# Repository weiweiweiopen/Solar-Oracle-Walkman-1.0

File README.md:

# Solar Oracle Walkman 1.0

**A portable, open-source instrument for exploring the electrical identity of handmade dye-sensitized solar cells (DSSCs).** Solar Oracle Walkman brings together I–V measurement, an e-paper display, interchangeable glass cells and a transparent SLA enclosure. A charging variant investigates harvesting energy from the same cell that is measured.

[Build guide](docs/build-guide.md) · [SLA assembly](docs/assembly.md) · [Verification and limitations](docs/reproducibility.md) · [Image gallery](docs/gallery.md) · [DSSC enrollment / verification library](https://github.com/weiweiweiopen/Solar-Oracle-Walkman-DSSC-Enrollment-and-Verification-Library)

The photograph shows a physical prototype. The source packages below distinguish the USB measurement board, the charging-board development revision and the earlier three-capacitor design. **This is an open development release, not a certified or fully validated production kit.**

## Choose a matched variant

| Variant | Electronics | Matching enclosure | Status |
|---|---|---|---|
| **CHARGE / ADG706** | November 3 1206 revision; 92 footprints, two copper layers; two 1.5 F supercapacitors, AEM10941, TPS61023 and K1 | R19_CHARGE_SUPERCAP | Latest charging hardware/CAD source; complete charging firmware and physical qualification remain open |
| **RAW / USB** | November 3 1206 revision; 39 footprints, two copper layers; no harvester, capacitors or K1 | R19_RAW | Separate USB measurement variant; see its firmware build and calibration status |
| **Legacy ADS122C04** | Earlier four-layer, 175-footprint, three-capacitor relay design | Do not use the R19 packages without a new fit review | Original project retained for reference; GPIO/startup firmware only |

Do not mix boards, GPIO definitions, BOMs or enclosure variants. The three-capacitor render is not the latest two-capacitor charging board, and its 4.5 F energy estimates do not apply to the current design.

## Hardware and fabrication files

| Download | CHARGE / ADG706 | RAW / USB |
|---|---|---|
| Native KiCad project | [Open project](hardware/charge-adg706/KiCad/Marc_USB.kicad_pro) | [Open project](hardware/raw/KiCad/Marc_USB.kicad_pro) |
| PCB source | [PCB](hardware/charge-adg706/KiCad/Marc_USB.kicad_pcb) | [PCB](hardware/raw/KiCad/Marc_USB.kicad_pcb) |
| Schematics and local libraries | [KiCad folder](hardware/charge-adg706/KiCad/) | [KiCad folder](hardware/raw/KiCad/) |
| Gerber + drill package | [Fabrication ZIP](hardware/charge-adg706/fabrication/Marc_USB_charge_adg706_single_DSSC_1206_20261103.zip) | [Fabrication ZIP](hardware/raw/fabrication/Marc_USB_raw_single_DSSC_1206_20261103.zip) |
| BOM and assembly references | [Assembly folder](hardware/charge-adg706/assembly/) | [Assembly folder](hardware/raw/assembly/) |
| DRC / ERC results | [Checks](hardware/charge-adg706/verification/) | [Checks](hardware/raw/verification/) |

Use **KiCad 10** with its standard libraries. Local symbols, footprints and model dependencies are included. The Gerber ZIPs are PCB fabrication outputs, not complete turnkey PCBA orders: missing/TBD procurement fields, assembly choices and DRC dispositions must be resolved before ordering.

## SLA enclosure — editable and printable

| Download | CHARGE_SUPERCAP | RAW |
|---|---|---|
| Two-part print ZIP, mm / 1:1 | [STL](enclosure/R19_CHARGE_SUPERCAP/R19_CHARGE_SUPERCAP_STL.zip) | [STL](enclosure/R19_RAW/R19_RAW_STL.zip) |
| Native FreeCAD assembly | [FCStd](enclosure/R19_CHARGE_SUPERCAP/R19_CHARGE_SUPERCAP.FCStd) | [FCStd](enclosure/R19_RAW/R19_RAW.FCStd) |
| Individual and assembled STEP | [STEP](enclosure/R19_CHARGE_SUPERCAP/STEP/) | [STEP](enclosure/R19_RAW/STEP/) |
| Editable source: CAD, Blender, geometry inputs, scripts and QA | [Source ZIP](enclosure/R19_CHARGE_SUPERCAP/R19_CHARGE_SUPERCAP_editable_source.zip) | [Source ZIP](enclosure/R19_RAW/R19_RAW_editable_source.zip) |
| Dimensions and original design notes | [Notes](enclosure/R19_CHARGE_SUPERCAP/README.md) | [Notes](enclosure/R19_RAW/README.md) |

R19 uses a removable full upper cover, 16 magnets and two conductive zebra strips. Its footprint is 84 × 142.4 mm. Use the [assembly guide](docs/assembly.md) for glass dimensions, fasteners, print precautions and the PCB insertion sequence. The archives include editable sources, not just presentation meshes.

## Firmware and first build

The [RAW firmware source](firmware/current/README.md) compiled successfully with PlatformIO; its 14 GPIOs and 16 nominal load values match the current RAW PCB. Start with the [build guide](docs/build-guide.md). Firmware is board-specific; flashing a similarly named ESP32 program is not a substitute for checking the GPIO map, ADC, load sequence and display revision. The legacy [GPIO/startup layer](firmware/README.md) is **not** the full measurement application for either current board.

## Front and rear renders

Charging concept visualization from the Murata presentation material. These show the two-capacitor arrangement; the current manufacturing geometry is defined by the KiCad and R19 files above, not by the rendered enclosure.

The [gallery](docs/gallery.md) also includes the earlier front and rear renders with **three blue supercapacitors**, kept separately for visual and design history.

## Verification before manufacture

Fresh checks of the packaged designs found:

- Both PCBs: **0 unrouted connections, 0 schematic/PCB parity differences, 0 ERC findings**.
- RAW: **10 courtyard-overlap errors, 5 warnings**. CHARGE: **10 courtyard-overlap errors, 9 warnings**. These are disclosed, not suppressed or called a clean DRC.
- Four enclosure parts: native CAD reopened as valid single solids; all four print meshes are closed, with no nonmanifold edges or self-intersections detected.
- Each R19 embedded PCB snapshot exactly matches the corresponding packaged current board.

Geometry checks and software compilation do not establish printed fit, electrical safety, calibration, cold-start performance, charge-cycle endurance or PUF security. See [reproducibility status](docs/reproducibility.md) for the outstanding work needed for an independently validated build.

## Credits and license

Developed by Shih Wei Chieh / Wise Mouse Culture, building on [Marc Dusseiller's I–V tester lineage](https://github.com/weiweiweiopen/IVcurve_tester). Existing MIT attribution is preserved in [LICENSE](LICENSE). Third-party libraries and model assets retain their own terms; see [THIRD_PARTY_NOTICES.md](THIRD_PARTY_NOTICES.md).

The separate [Solar Oracle Walkman data library](https://weiweiweiopen.github.io/Solar-Oracle-Walkman-DSSC-Enrollment-and-Verification-Library/) provides the measurement-library context; it is not the hardware manufacturing package.

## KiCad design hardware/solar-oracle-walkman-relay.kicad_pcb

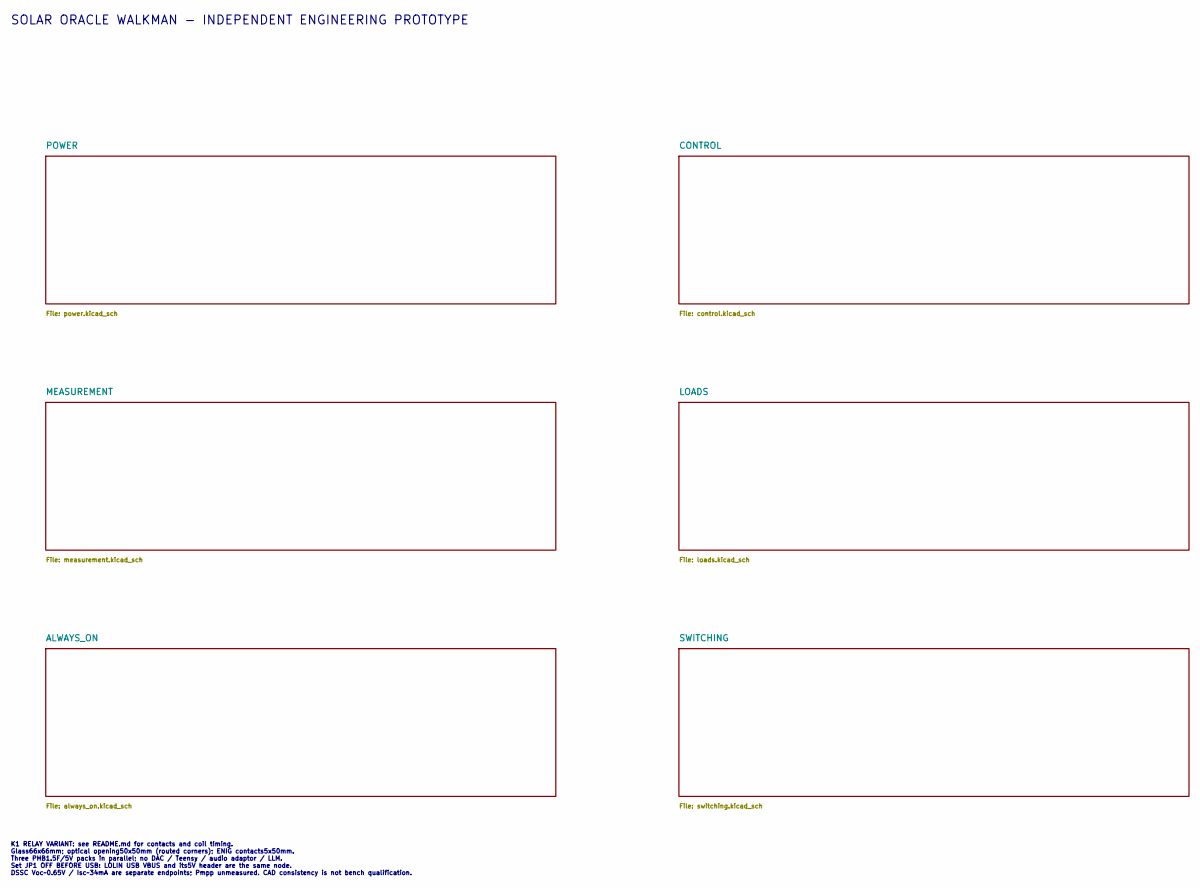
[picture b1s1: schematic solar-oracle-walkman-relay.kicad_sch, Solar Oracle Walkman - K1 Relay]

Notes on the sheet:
SOLAR ORACLE WALKMAN - INDEPENDENT ENGINEERING PROTOTYPE
K1 RELAY VARIANT: see README.md for contacts and coil timing. Glass66x66mm; optical opening50x50mm (routed corners); ENIG contacts5x50mm. Three PHB1.5F/5V packs in parallel; no DAC / Teensy / audio adaptor / LLM. Set JP1 OFF BEFORE USB: LOLIN USB VBUS and its5V header are the same node. DSSC Voc~0.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

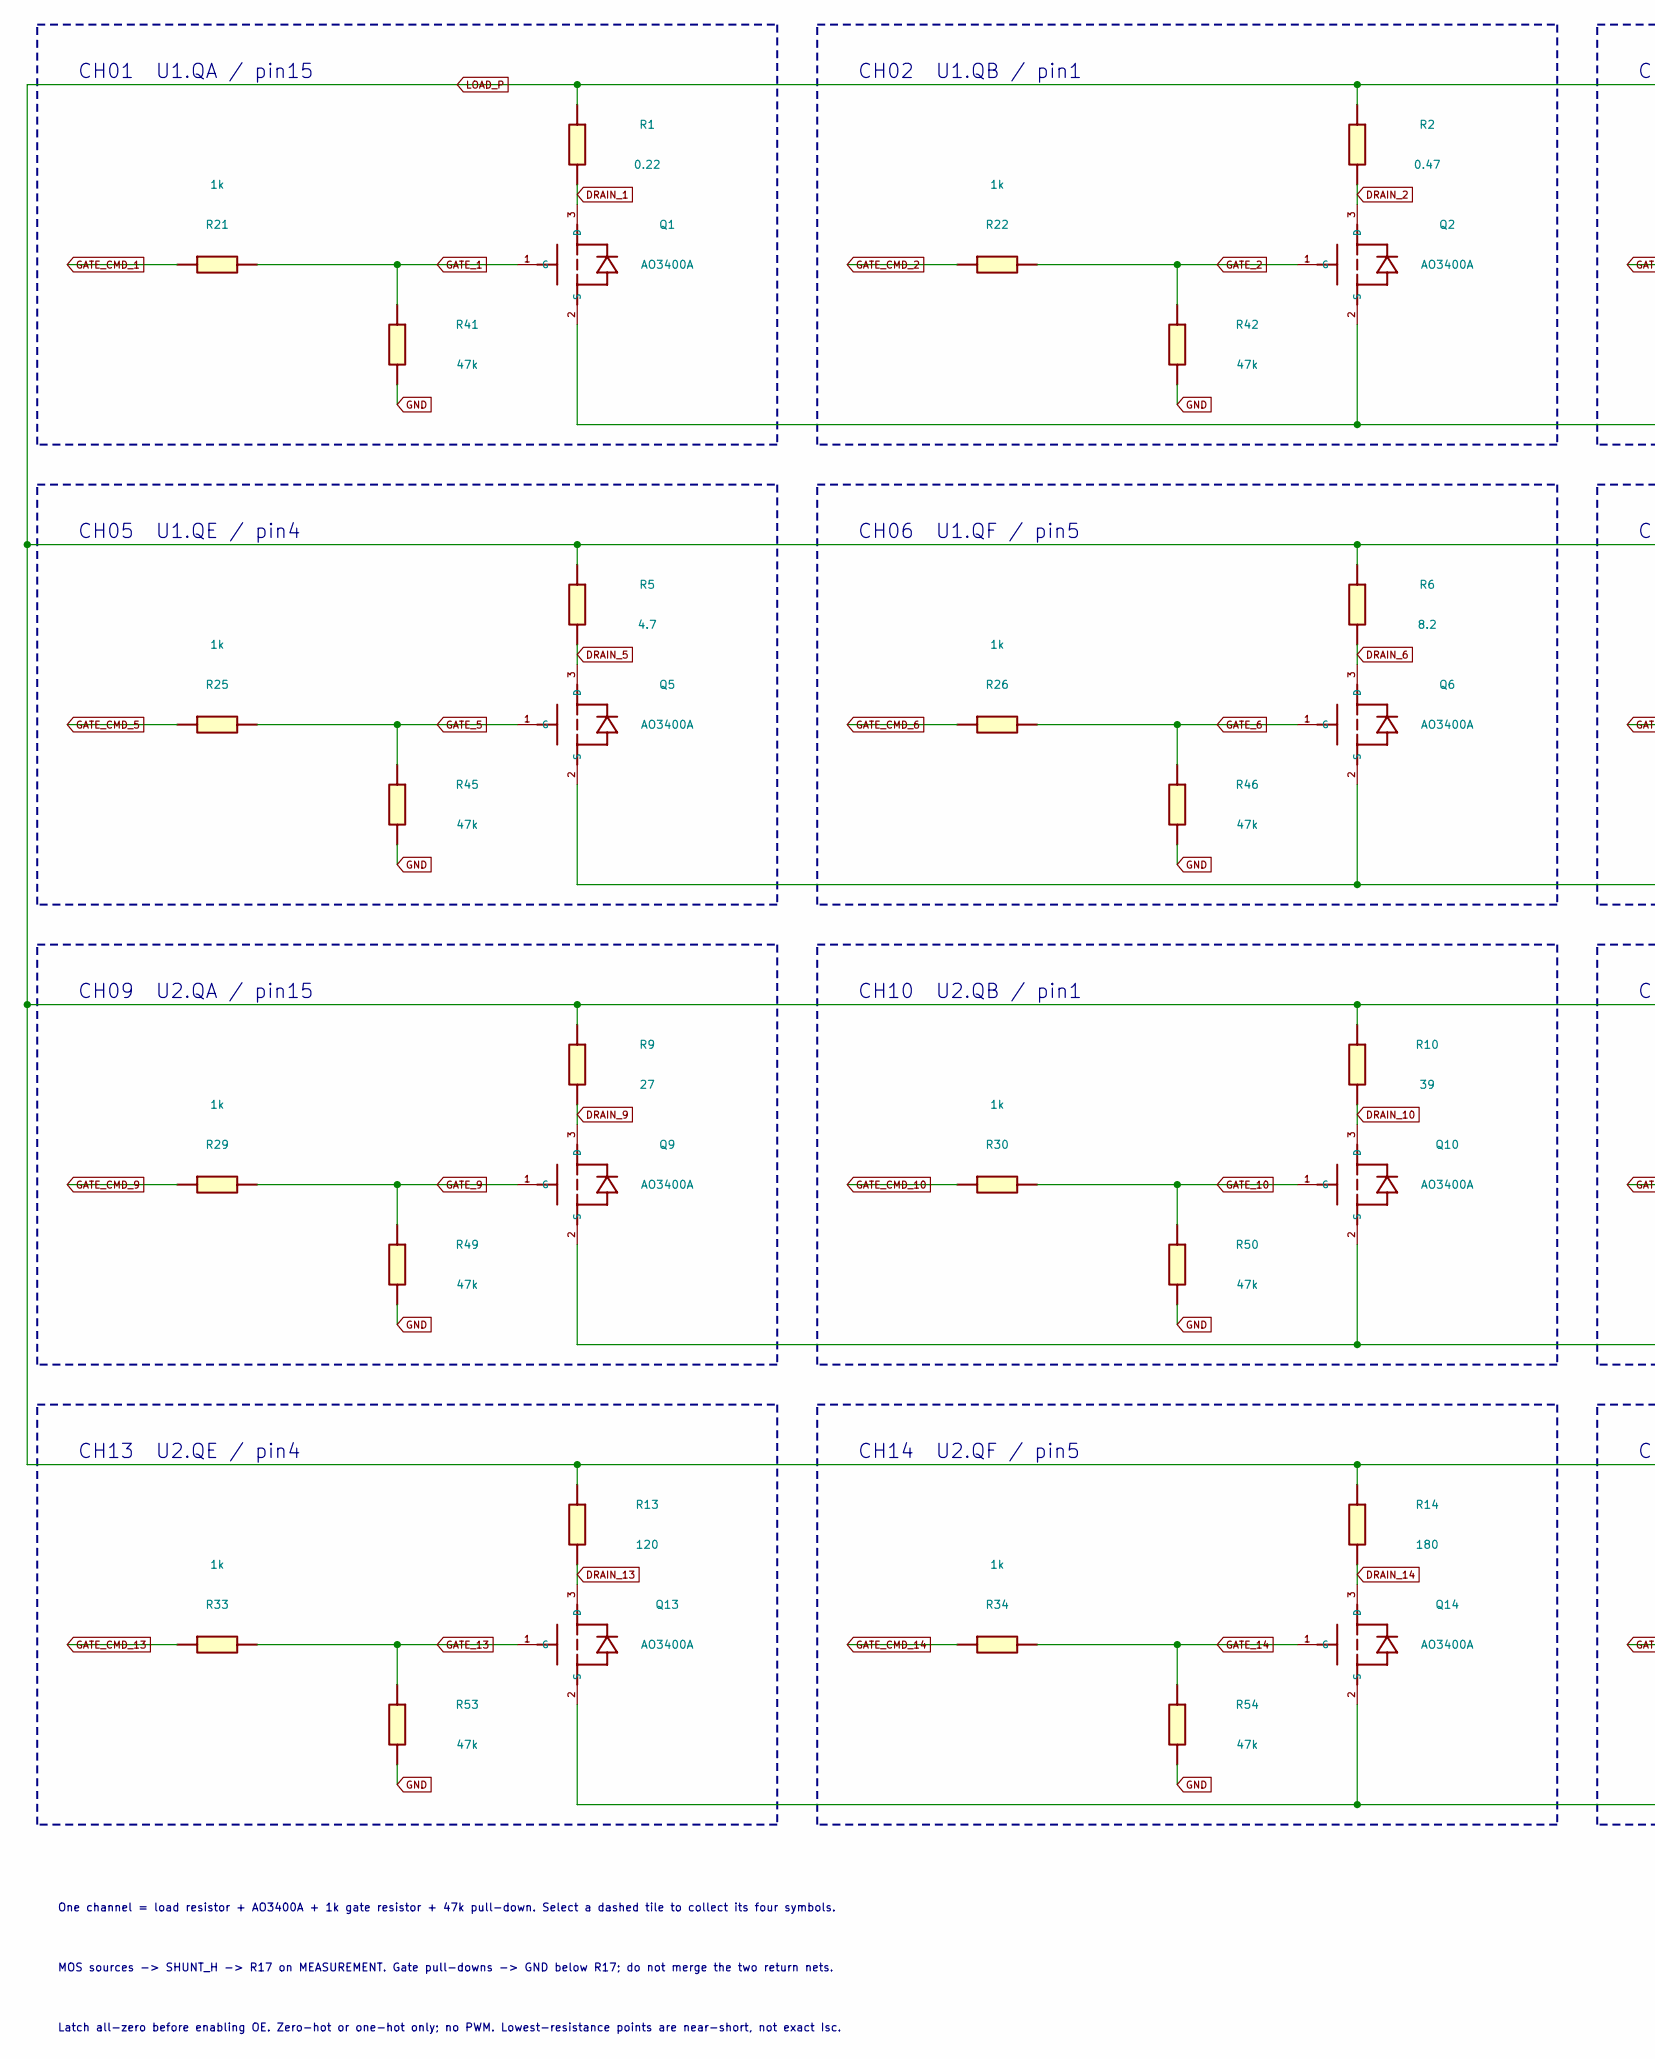
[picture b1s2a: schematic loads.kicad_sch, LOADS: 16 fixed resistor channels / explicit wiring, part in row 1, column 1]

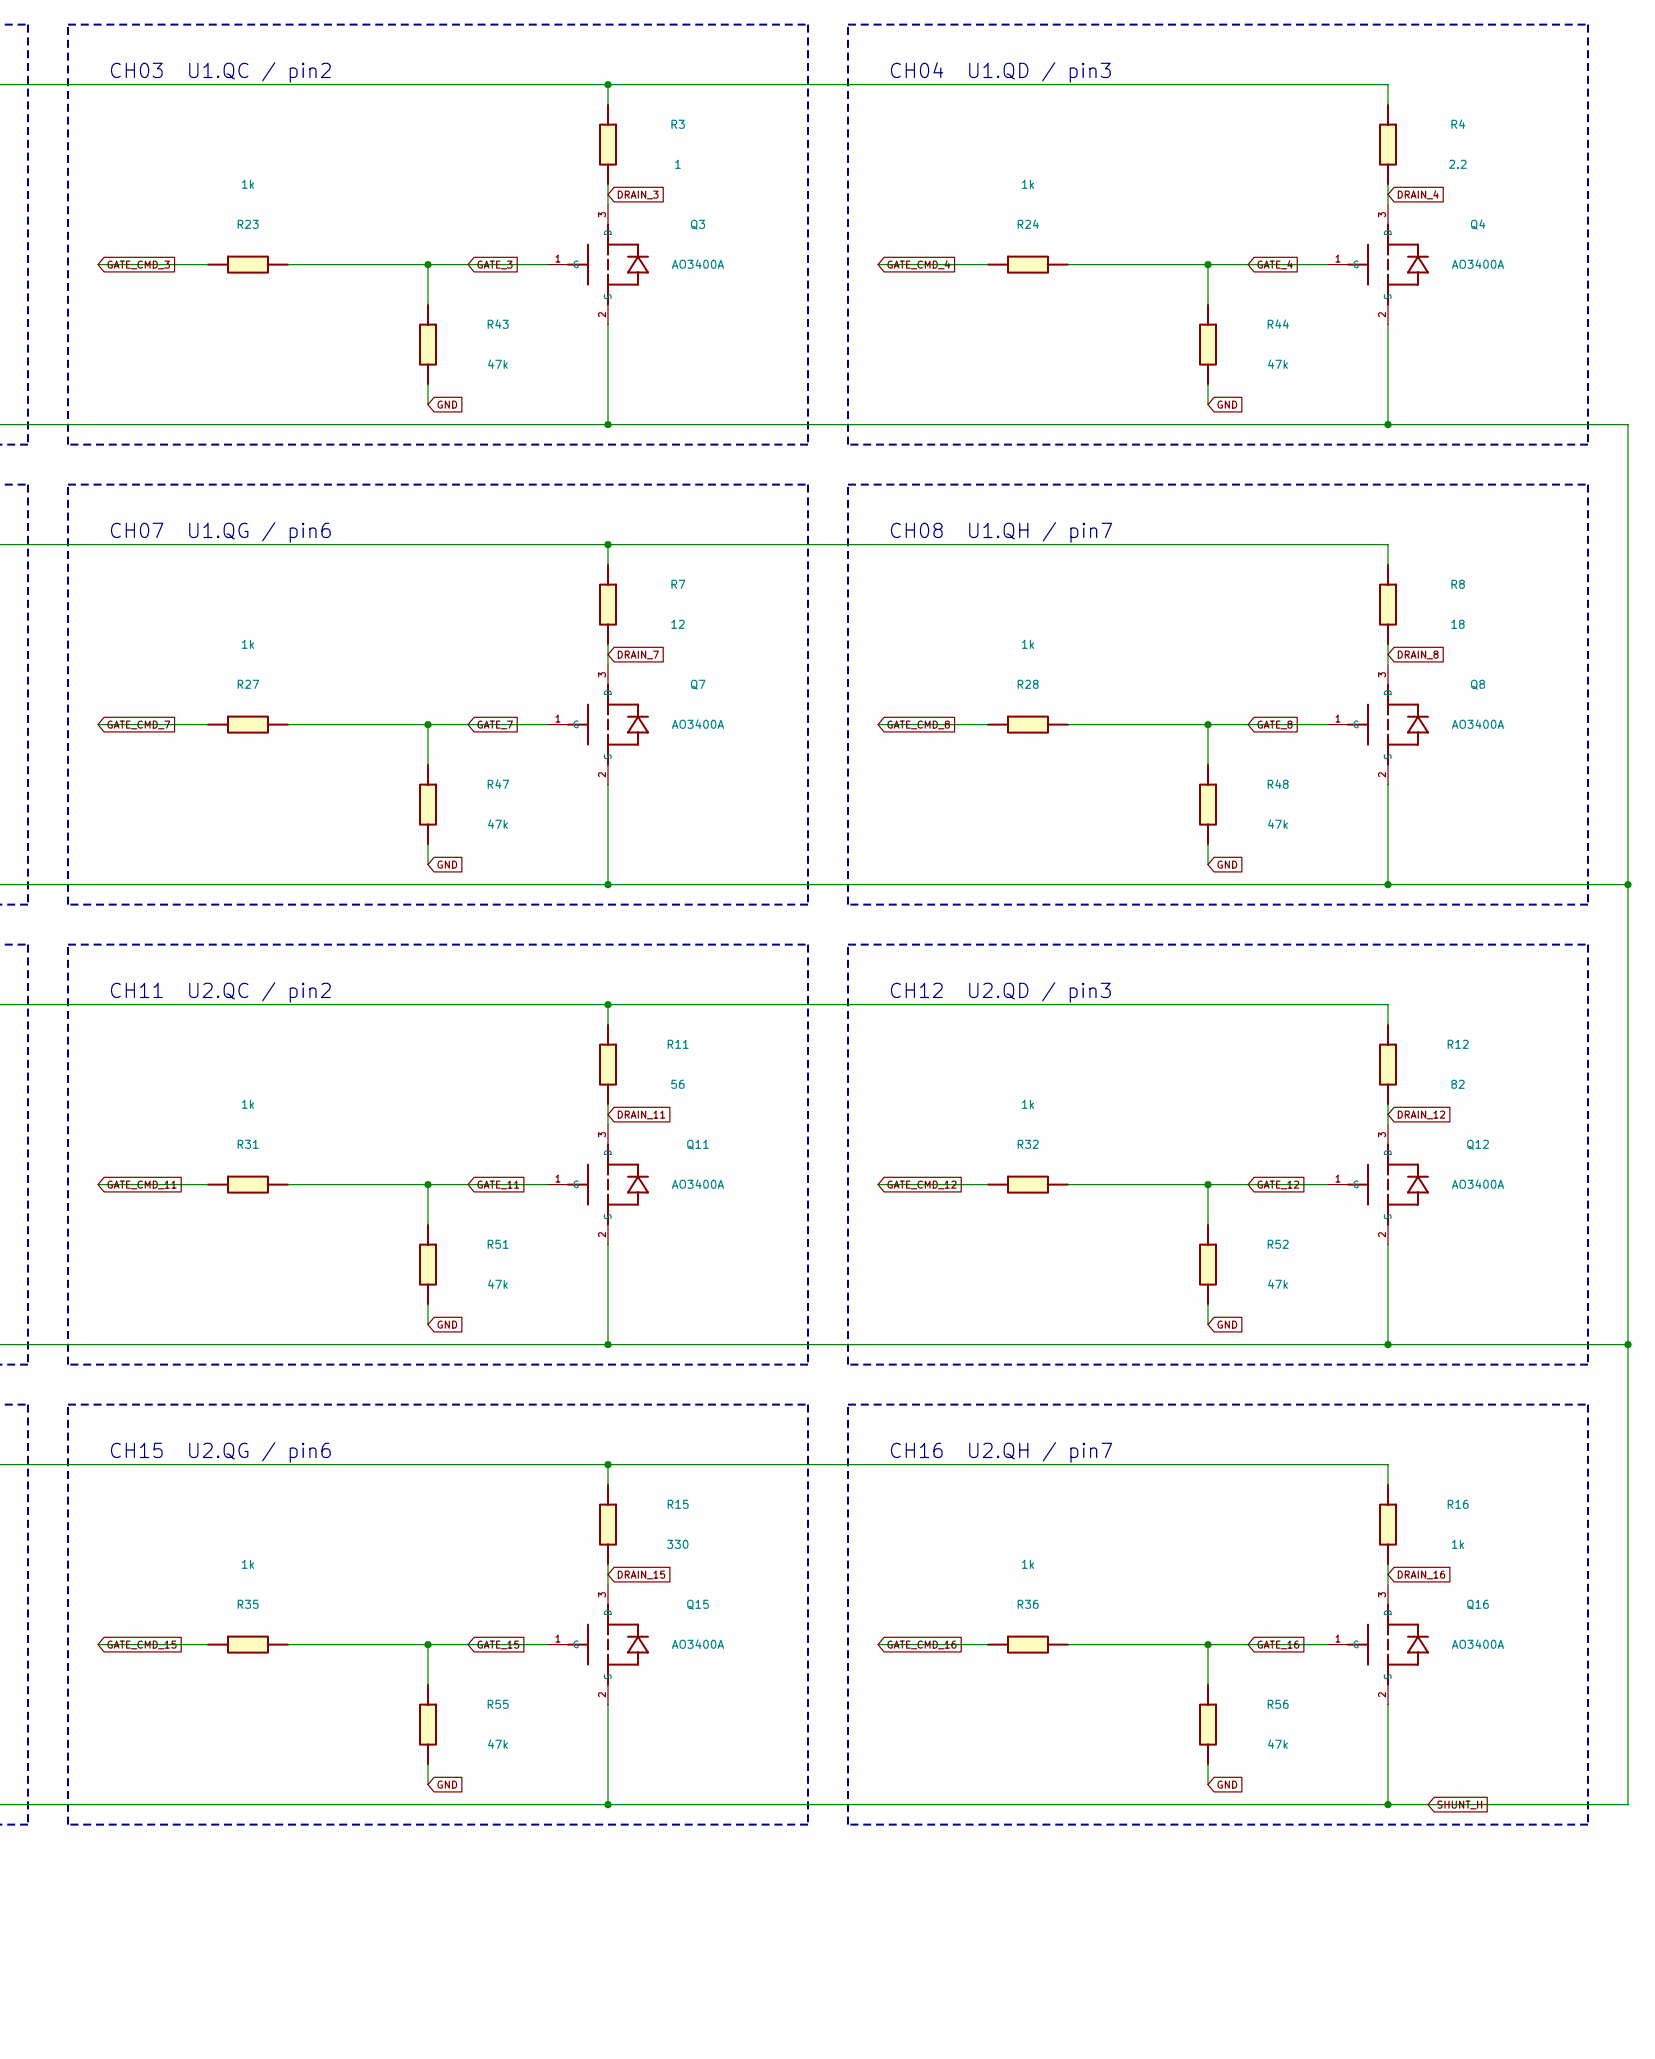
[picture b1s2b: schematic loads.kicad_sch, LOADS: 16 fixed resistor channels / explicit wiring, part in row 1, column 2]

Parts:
Q1, Q2, Q3, Q4, Q5, Q6, Q7, Q8, Q9, Q10, Q11, Q12, Q13, Q14, Q15, Q16: AO3400A; SOT-23; MPN AO3400A
R1: 0.22; R_1206_3216Metric; MPN RL1206FR-070R22L
R2: 0.47; R_1206_3216Metric; MPN RL1206FR-070R47L
R3: 1; R_1206_3216Metric; MPN RT1206BRD071RL
R4: 2.2; R_1206_3216Metric; MPN RT1206BRD072R2L
R5: 4.7; R_1206_3216Metric; MPN RT1206BRD074R7L
R6: 8.2; R_1206_3216Metric; MPN RT1206BRD078R2L
R7: 12; R_1206_3216Metric; MPN RT1206BRD0712RL
R8: 18; R_1206_3216Metric; MPN RT1206BRD0718RL
R9: 27; R_1206_3216Metric; MPN RT1206BRD0727RL
R10: 39; R_1206_3216Metric; MPN RT1206BRD0739RL
R11: 56; R_1206_3216Metric; MPN RT1206BRD0756RL
R12: 82; R_1206_3216Metric; MPN RT1206BRD0782RL
R13: 120; R_1206_3216Metric; MPN RT1206BRD07120RL
R14: 180; R_1206_3216Metric; MPN RT1206BRD07180RL
R15: 330; R_1206_3216Metric; MPN RT1206BRD07330RL
R16: 1k; R_1206_3216Metric; MPN RT1206BRD071KL
R21, R22, R23, R24, R25, R26, R27, R28, R29, R30, R31, R32, R33, R34, R35, R36: 1k; R_0603_1608Metric; MPN RC0603FR-071KL
R41, R42, R43, R44, R45, R46, R47, R48, R49, R50, R51, R52, R53, R54, R55, R56: 47k; R_0603_1608Metric; MPN RC0603FR-0747KL

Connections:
DRAIN_1: Q1.3 (D), R1.2
DRAIN_2: Q2.3 (D), R2.2
DRAIN_3: Q3.3 (D), R3.2
DRAIN_4: Q4.3 (D), R4.2
DRAIN_5: Q5.3 (D), R5.2
DRAIN_6: Q6.3 (D), R6.2
DRAIN_7: Q7.3 (D), R7.2
DRAIN_8: Q8.3 (D), R8.2
DRAIN_9: Q9.3 (D), R9.2
DRAIN_10: Q10.3 (D), R10.2
DRAIN_11: Q11.3 (D), R11.2
DRAIN_12: Q12.3 (D), R12.2
DRAIN_13: Q13.3 (D), R13.2
DRAIN_14: Q14.3 (D), R14.2
DRAIN_15: Q15.3 (D), R15.2
DRAIN_16: Q16.3 (D), R16.2
GATE_1: Q1.1 (G), R21.2, R41.1
GATE_2: Q2.1 (G), R22.2, R42.1
GATE_3: Q3.1 (G), R23.2, R43.1
GATE_4: Q4.1 (G), R24.2, R44.1
GATE_5: Q5.1 (G), R25.2, R45.1
GATE_6: Q6.1 (G), R26.2, R46.1
GATE_7: Q7.1 (G), R27.2, R47.1
GATE_8: Q8.1 (G), R28.2, R48.1
GATE_9: Q9.1 (G), R29.2, R49.1
GATE_10: Q10.1 (G), R30.2, R50.1
GATE_11: Q11.1 (G), R31.2, R51.1
GATE_12: Q12.1 (G), R32.2, R52.1
GATE_13: Q13.1 (G), R33.2, R53.1
GATE_14: Q14.1 (G), R34.2, R54.1
GATE_15: Q15.1 (G), R35.2, R55.1
GATE_16: Q16.1 (G), R36.2, R56.1
GATE_CMD_1: R21.1; also elsewhere on the board
GATE_CMD_2: R22.1; also elsewhere on the board
GATE_CMD_3: R23.1; also elsewhere on the board
GATE_CMD_4: R24.1; also elsewhere on the board
GATE_CMD_5: R25.1; also elsewhere on the board
GATE_CMD_6: R26.1; also elsewhere on the board
GATE_CMD_7: R27.1; also elsewhere on the board
GATE_CMD_8: R28.1; also elsewhere on the board
GATE_CMD_9: R29.1; also elsewhere on the board
GATE_CMD_10: R30.1; also elsewhere on the board
GATE_CMD_11: R31.1; also elsewhere on the board
GATE_CMD_12: R32.1; also elsewhere on the board
GATE_CMD_13: R33.1; also elsewhere on the board
GATE_CMD_14: R34.1; also elsewhere on the board
GATE_CMD_15: R35.1; also elsewhere on the board
GATE_CMD_16: R36.1; also elsewhere on the board
GND: R41.2, R42.2, R43.2, R44.2, R45.2, R46.2, R47.2, R48.2, R49.2, R50.2, R51.2, R52.2, R53.2, R54.2, R55.2, R56.2; also elsewhere on the board
LOAD_P: R1.1, R2.1, R3.1, R4.1, R5.1, R6.1, R7.1, R8.1, R9.1, R10.1, R11.1, R12.1, R13.1, R14.1, R15.1, R16.1; also elsewhere on the board
SHUNT_H: Q1.2 (S), Q2.2 (S), Q3.2 (S), Q4.2 (S), Q5.2 (S), Q6.2 (S), Q7.2 (S), Q8.2 (S), Q9.2 (S), Q10.2 (S), Q11.2 (S), Q12.2 (S), Q13.2 (S), Q14.2 (S), Q15.2 (S), Q16.2 (S); also elsewhere on the board

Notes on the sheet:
CH07 U1.QG / pin6
CH14 U2.QF / pin5
CH11 U2.QC / pin2
CH10 U2.QB / pin1
CH12 U2.QD / pin3
CH05 U1.QE / pin4
CH03 U1.QC / pin2
MOS sources -> SHUNT_H -> R17 on MEASUREMENT. Gate pull-downs -> GND below R17; do not merge the two return nets.
One channel = load resistor + AO3400A + 1k gate resistor + 47k pull-down. Select a dashed tile to collect its four symbols.
Latch all-zero before enabling OE. Zero-hot or one-hot only; no PWM. Lowest-resistance points are near-short, not exact Isc.
CH15 U2.QG / pin6
CH01 U1.QA / pin15
CH09 U2.QA / pin15
CH02 U1.QB / pin1
CH04 U1.QD / pin3
CH16 U2.QH / pin7
CH13 U2.QE / pin4
CH06 U1.QF / pin5
CH08 U1.QH / pin7

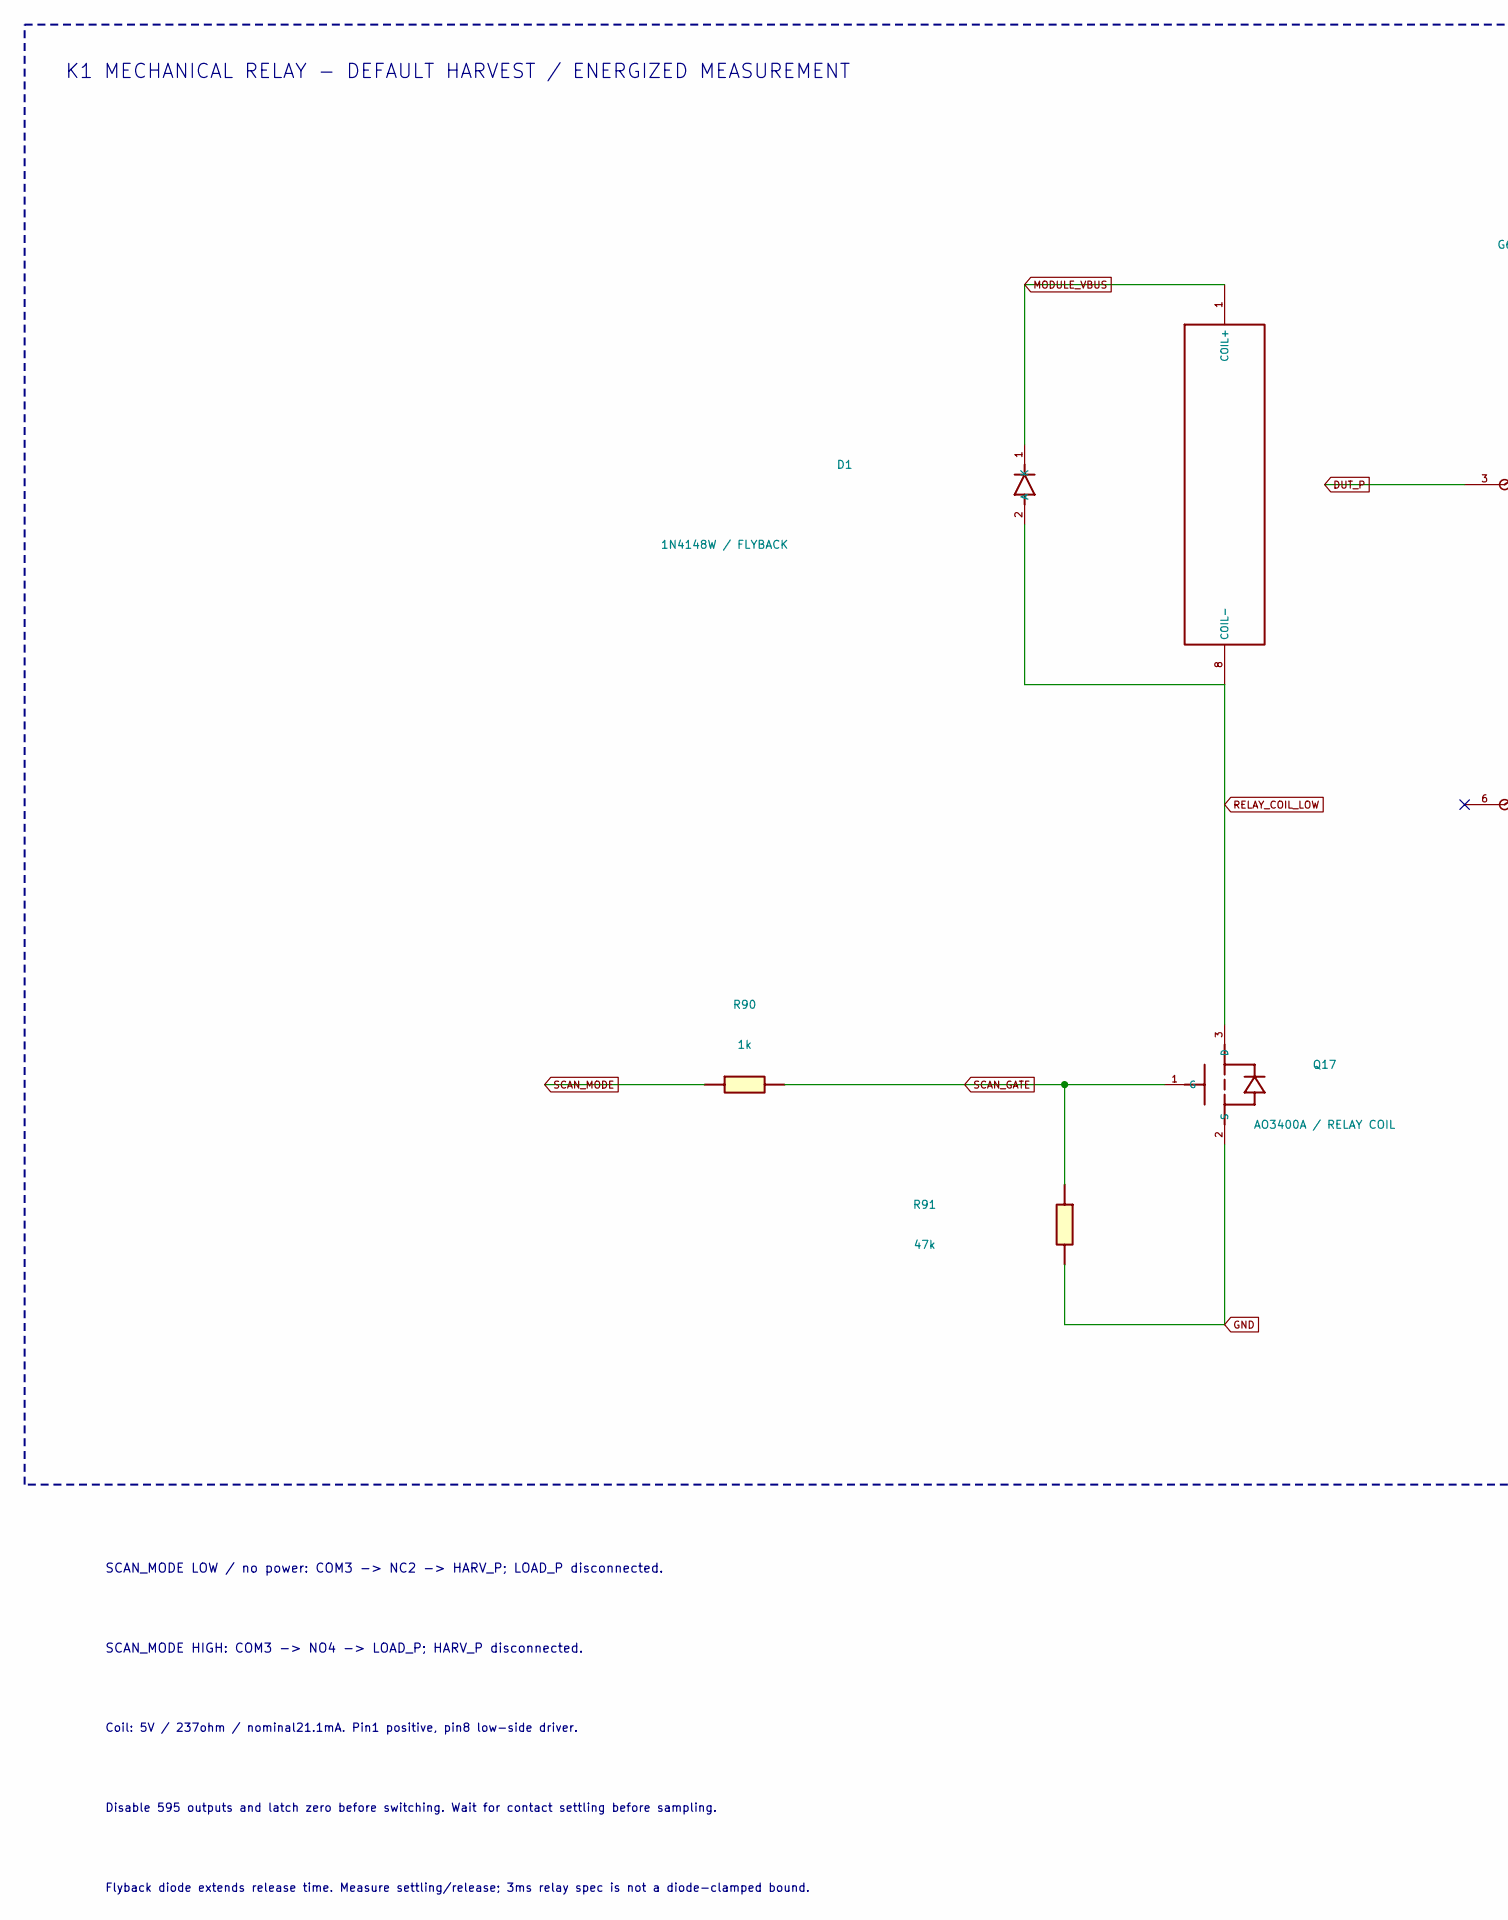
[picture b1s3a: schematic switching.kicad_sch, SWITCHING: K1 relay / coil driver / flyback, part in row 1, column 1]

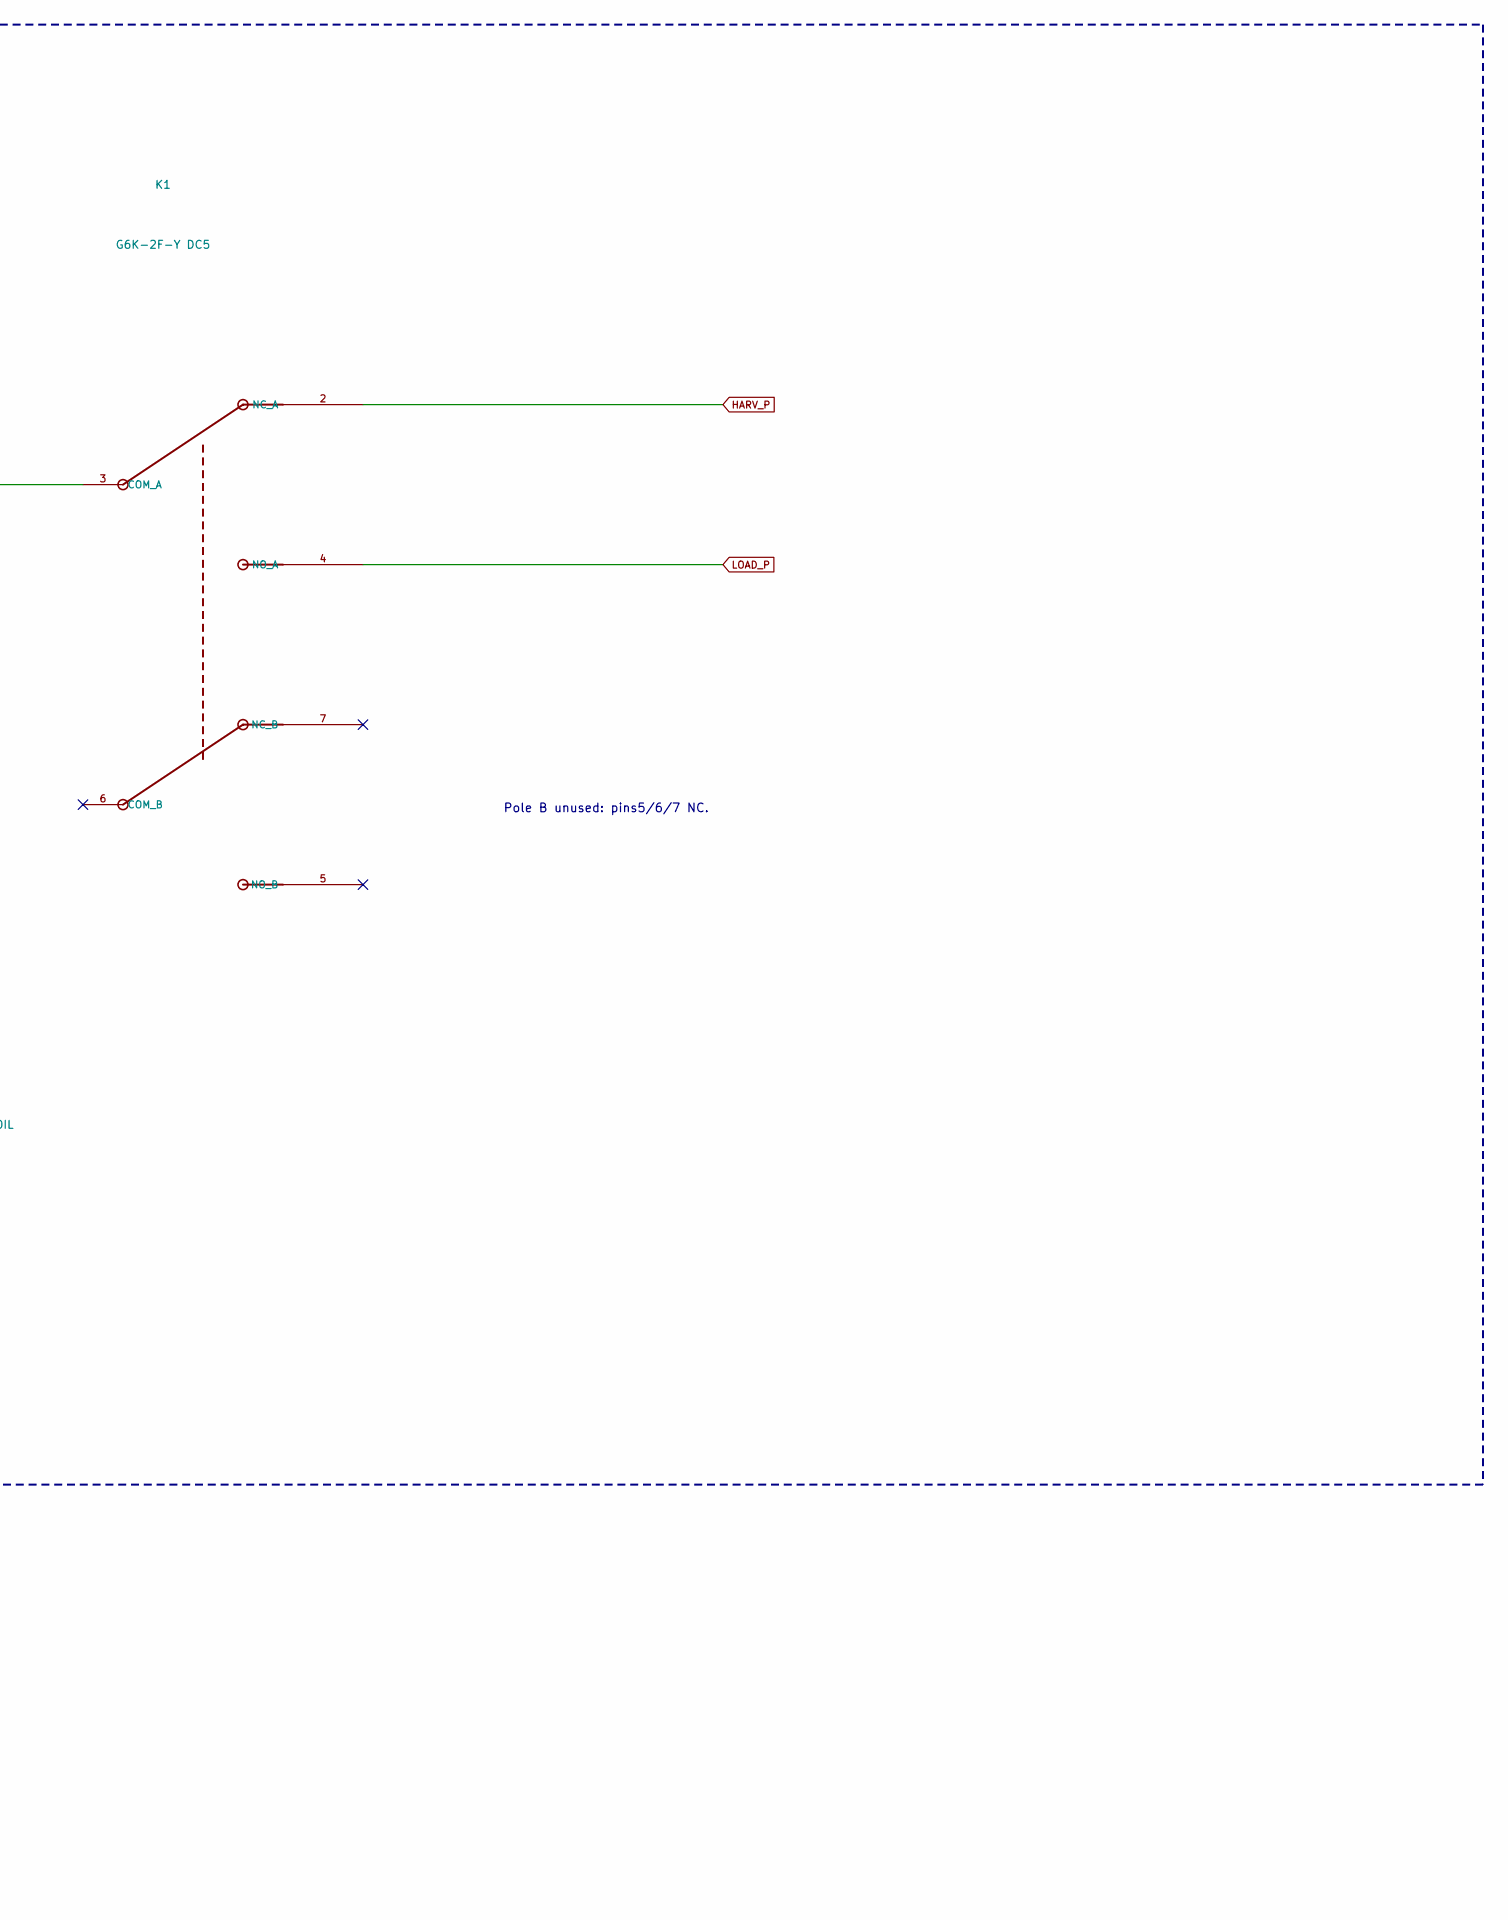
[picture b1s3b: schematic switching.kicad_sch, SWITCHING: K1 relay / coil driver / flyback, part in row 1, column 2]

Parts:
D1: 1N4148W / FLYBACK; D_SOD-123; MPN 1N4148W-7-F
K1: G6K-2F-Y DC5; G6K_2F_Y; MPN G6K-2F-Y-TR DC5
Q17: AO3400A / RELAY COIL; SOT-23; MPN AO3400A
R90: 1k; R_0603_1608Metric; MPN RC0603FR-071KL
R91: 47k; R_0603_1608Metric; MPN RC0603FR-0747KL

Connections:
DUT_P: K1.3 (COM_A); also elsewhere on the board
GND: Q17.2 (S), R91.2; also elsewhere on the board
HARV_P: K1.2 (NC_A); also elsewhere on the board
LOAD_P: K1.4 (NO_A); also elsewhere on the board
MODULE_VBUS: D1.1 (K), K1.1 (COIL+); also elsewhere on the board
RELAY_COIL_LOW: D1.2 (A), K1.8 (COIL-), Q17.3 (D)
SCAN_GATE: Q17.1 (G), R90.2, R91.1
SCAN_MODE: R90.1; also elsewhere on the board

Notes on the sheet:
SCAN_MODE HIGH: COM3 -> NO4 -> LOAD_P; HARV_P disconnected.
Flyback diode extends release time. Measure settling/release; 3ms relay spec is not a diode-clamped bound.
Coil: 5V / 237ohm / nominal21.1mA. Pin1 positive, pin8 low-side driver.
SCAN_MODE LOW / no power: COM3 -> NC2 -> HARV_P; LOAD_P disconnected.
K1 MECHANICAL RELAY - DEFAULT HARVEST / ENERGIZED MEASUREMENT
Disable 595 outputs and latch zero before switching. Wait for contact settling before sampling.
Pole B unused: pins5/6/7 NC.
